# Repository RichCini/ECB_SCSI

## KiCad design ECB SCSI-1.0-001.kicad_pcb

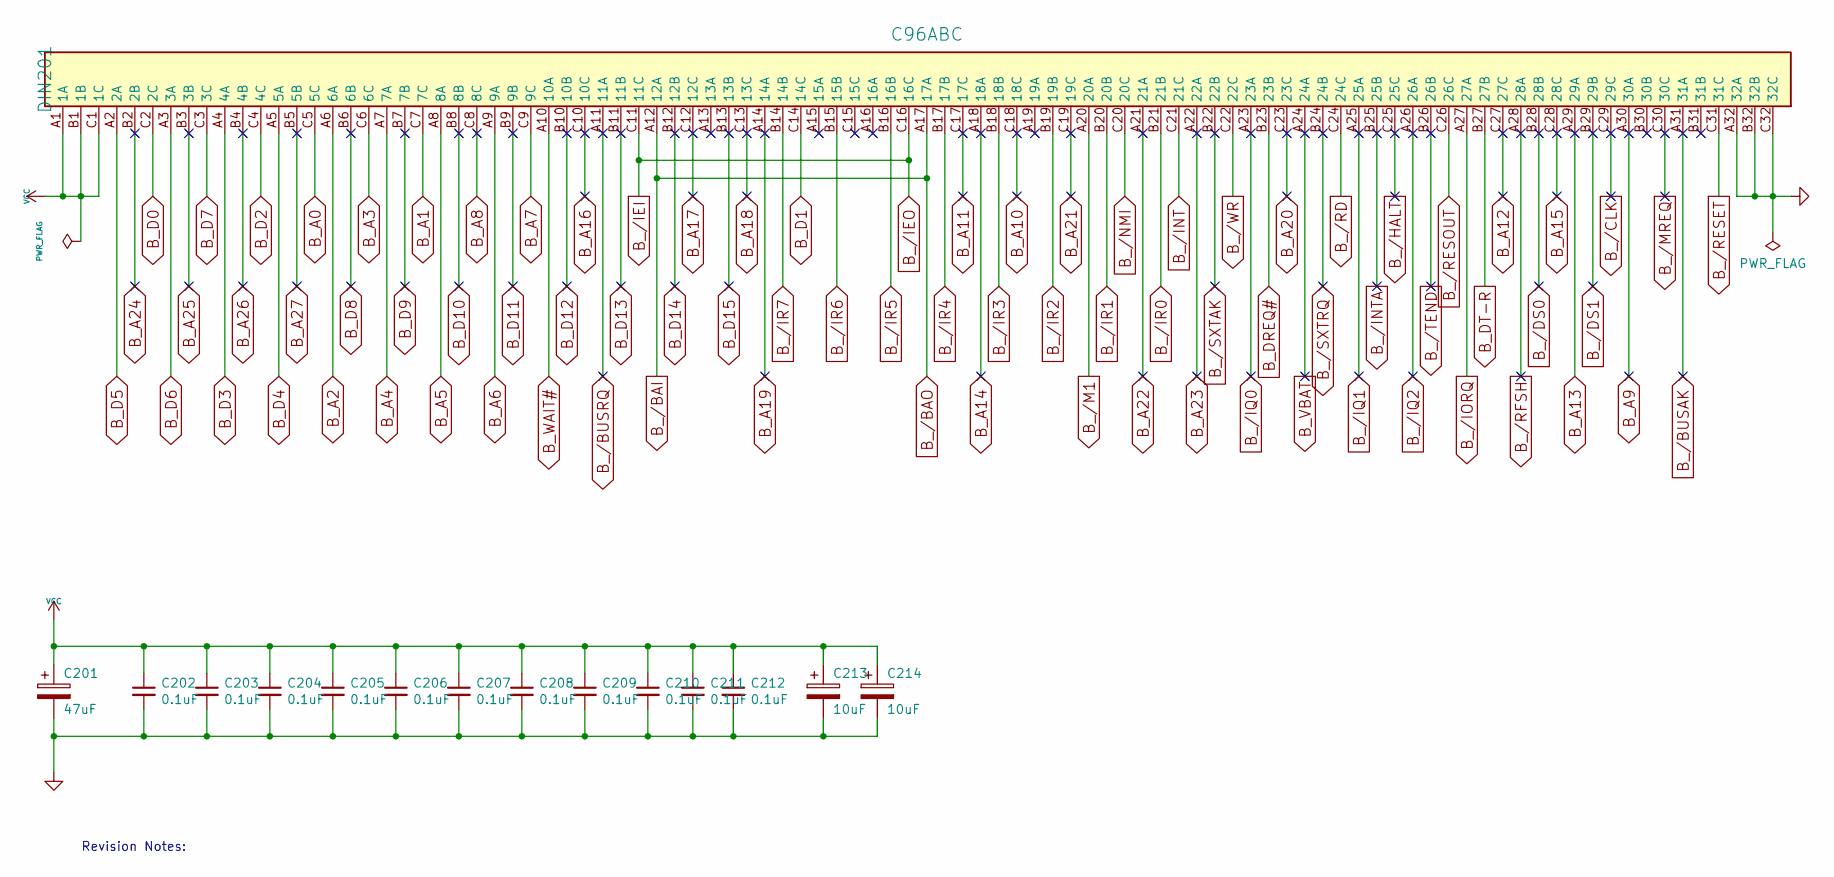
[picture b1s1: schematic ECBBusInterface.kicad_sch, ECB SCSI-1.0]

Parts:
C201: 47uF; CP_Radial_D7.5mm_P2.50mm
C202, C203, C204, C205, C206, C207, C208, C209, C210, C211, C212: 0.1uF; C_Disc_D4.3mm_W1.9mm_P5.00mm
C213, C214: 10uF; CP_Radial_D4.0mm_P1.50mm
DIN201: C96ABC; C96ABCM-RA

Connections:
B_/BAI: DIN201.A12 (12A), DIN201.A17 (17A)
B_/BUSAK: DIN201.A31 (31A)
B_/BUSRQ: DIN201.A11 (11A)
B_/CLK: DIN201.C29 (29C)
B_/DS0: DIN201.B28 (28B)
B_/DS1: DIN201.B29 (29B)
B_/HALT: DIN201.C25 (25C)
B_/IEI: DIN201.C11 (11C), DIN201.C16 (16C)
B_/INT: DIN201.C21 (21C); also elsewhere on the board
B_/INTA: DIN201.B25 (25B)
B_/IORQ: DIN201.A27 (27A); also elsewhere on the board
B_/IQ0: DIN201.A23 (23A)
B_/IQ1: DIN201.A25 (25A)
B_/IQ2: DIN201.A26 (26A)
B_/IR0: DIN201.B21 (21B); also elsewhere on the board
B_/IR1: DIN201.B20 (20B); also elsewhere on the board
B_/IR2: DIN201.B19 (19B); also elsewhere on the board
B_/IR3: DIN201.B18 (18B); also elsewhere on the board
B_/IR4: DIN201.B17 (17B); also elsewhere on the board
B_/IR5: DIN201.B16 (16B); also elsewhere on the board
B_/IR6: DIN201.B15 (15B); also elsewhere on the board
B_/IR7: DIN201.B14 (14B); also elsewhere on the board
B_/M1: DIN201.A20 (20A); also elsewhere on the board
B_/MREQ: DIN201.C30 (30C)
B_/NMI: DIN201.C20 (20C); also elsewhere on the board
B_/RD: DIN201.C24 (24C); also elsewhere on the board
B_/RESET: DIN201.C31 (31C); also elsewhere on the board
B_/RESOUT: DIN201.C26 (26C); also elsewhere on the board
B_/RFSH: DIN201.A28 (28A)
B_/SXTAK: DIN201.B22 (22B)
B_/SXTRQ: DIN201.B24 (24B)
B_/TEND: DIN201.B26 (26B)
B_/WR: DIN201.C22 (22C); also elsewhere on the board
B_A0: DIN201.C5 (5C); also elsewhere on the board
B_A1: DIN201.C7 (7C); also elsewhere on the board
B_A2: DIN201.A6 (6A); also elsewhere on the board
B_A3: DIN201.C6 (6C); also elsewhere on the board
B_A4: DIN201.A7 (7A); also elsewhere on the board
B_A5: DIN201.A8 (8A); also elsewhere on the board
B_A6: DIN201.A9 (9A); also elsewhere on the board
B_A7: DIN201.C9 (9C); also elsewhere on the board
B_A8: DIN201.C8 (8C)
B_A9: DIN201.A30 (30A)
B_A10: DIN201.C18 (18C)
B_A11: DIN201.C17 (17C)
B_A12: DIN201.C27 (27C)
B_A13: DIN201.A29 (29A)
B_A14: DIN201.A18 (18A)
B_A15: DIN201.C28 (28C)
B_A16: DIN201.C10 (10C)
B_A17: DIN201.C12 (12C)
B_A18: DIN201.C13 (13C)
B_A19: DIN201.A14 (14A)
B_A20: DIN201.C23 (23C)
B_A21: DIN201.C19 (19C)
B_A22: DIN201.A21 (21A)
B_A23: DIN201.A22 (22A)
B_A24: DIN201.B2 (2B)
B_A25: DIN201.B3 (3B)
B_A26: DIN201.B4 (4B)
B_A27: DIN201.B5 (5B)
B_D0: DIN201.C2 (2C); also elsewhere on the board
B_D1: DIN201.C14 (14C); also elsewhere on the board
B_D2: DIN201.C4 (4C); also elsewhere on the board
B_D3: DIN201.A4 (4A); also elsewhere on the board
B_D4: DIN201.A5 (5A); also elsewhere on the board
B_D5: DIN201.A2 (2A); also elsewhere on the board
B_D6: DIN201.A3 (3A); also elsewhere on the board
B_D7: DIN201.C3 (3C); also elsewhere on the board
B_D8: DIN201.B6 (6B)
B_D9: DIN201.B7 (7B)
B_D10: DIN201.B8 (8B)
B_D11: DIN201.B9 (9B)
B_D12: DIN201.B10 (10B)
B_D13: DIN201.B11 (11B)
B_D14: DIN201.B12 (12B)
B_D15: DIN201.B13 (13B)
B_DREQ#: DIN201.B23 (23B); also elsewhere on the board
B_DT-R: DIN201.B27 (27B); also elsewhere on the board
B_VBAT: DIN201.A24 (24A)
B_WAIT#: DIN201.A10 (10A); also elsewhere on the board
GND: C201.2, C202.2, C203.2, C204.2, C205.2, C206.2, C207.2, C208.2, C209.2, C210.2, C211.2, C212.2, C213.2, C214.2, DIN201.A32 (32A), DIN201.B32 (32B), DIN201.C32 (32C); also elsewhere on the board
VCC: C201.1, C202.1, C203.1, C204.1, C205.1, C206.1, C207.1, C208.1, C209.1, C210.1, C211.1, C212.1, C213.1, C214.1, DIN201.A1 (1A), DIN201.B1 (1B), DIN201.C1 (1C); also elsewhere on the board

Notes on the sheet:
Revision Notes:

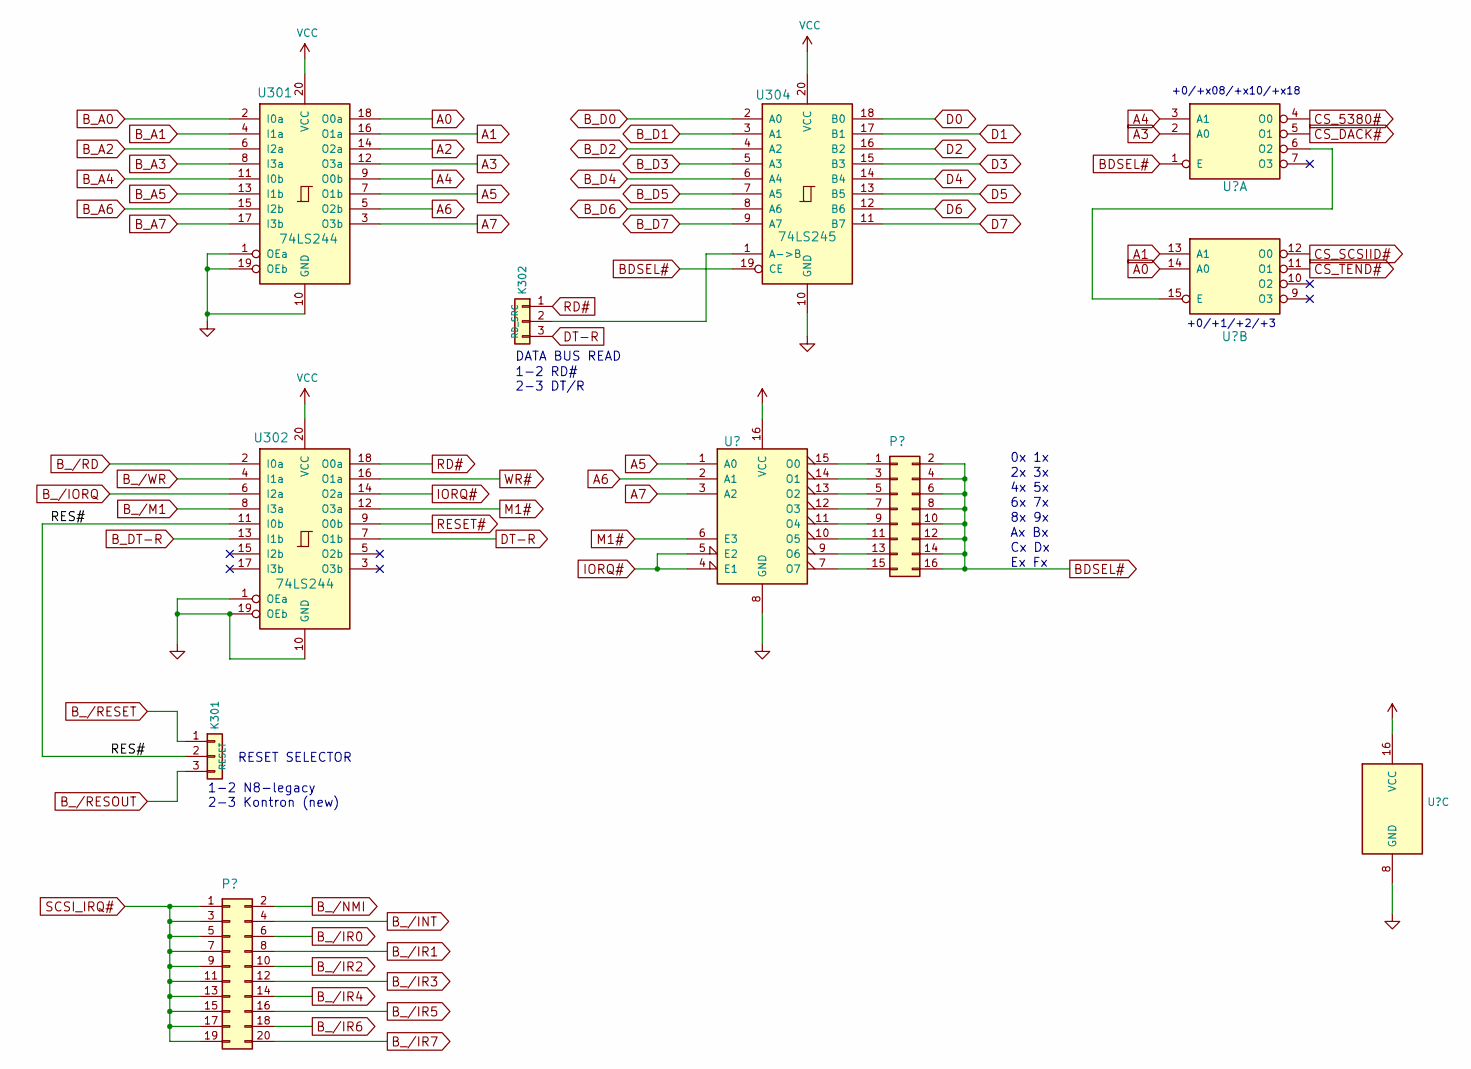
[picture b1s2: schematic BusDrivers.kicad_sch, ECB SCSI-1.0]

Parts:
K301: RESET; PinHeader_1x03_P2.54mm_Vertical
K302: RD_SRC; PinHeader_1x03_P2.54mm_Vertical
U301, U302: 74LS244; DIP-20_W7.62mm_Socket
U304: 74LS245; DIP-20_W7.62mm_Socket

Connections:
/Bus Drivers/RES#: K301.2, U302.11 (I0b)
A0: U301.18 (O0a); also elsewhere on the board
A1: U301.16 (O1a); also elsewhere on the board
A2: U301.14 (O2a); also elsewhere on the board
A3: U301.12 (O3a); also elsewhere on the board
A4: U301.9 (O0b); also elsewhere on the board
A5: U301.7 (O1b); also elsewhere on the board
A6: U301.5 (O2b); also elsewhere on the board
A7: U301.3 (O3b); also elsewhere on the board
BDSEL#: U304.19 (CE); also elsewhere on the board
B_/IORQ: U302.6 (I2a); also elsewhere on the board
B_/M1: U302.8 (I3a); also elsewhere on the board
B_/RD: U302.2 (I0a); also elsewhere on the board
B_/RESET: K301.1; also elsewhere on the board
B_/RESOUT: K301.3; also elsewhere on the board
B_/WR: U302.4 (I1a); also elsewhere on the board
B_A0: U301.2 (I0a); also elsewhere on the board
B_A1: U301.4 (I1a); also elsewhere on the board
B_A2: U301.6 (I2a); also elsewhere on the board
B_A3: U301.8 (I3a); also elsewhere on the board
B_A4: U301.11 (I0b); also elsewhere on the board
B_A5: U301.13 (I1b); also elsewhere on the board
B_A6: U301.15 (I2b); also elsewhere on the board
B_A7: U301.17 (I3b); also elsewhere on the board
B_D0: U304.2 (A0); also elsewhere on the board
B_D1: U304.3 (A1); also elsewhere on the board
B_D2: U304.4 (A2); also elsewhere on the board
B_D3: U304.5 (A3); also elsewhere on the board
B_D4: U304.6 (A4); also elsewhere on the board
B_D5: U304.7 (A5); also elsewhere on the board
B_D6: U304.8 (A6); also elsewhere on the board
B_D7: U304.9 (A7); also elsewhere on the board
B_DT-R: U302.13 (I1b); also elsewhere on the board
D0: U304.18 (B0); also elsewhere on the board
D1: U304.17 (B1); also elsewhere on the board
D2: U304.16 (B2); also elsewhere on the board
D3: U304.15 (B3); also elsewhere on the board
D4: U304.14 (B4); also elsewhere on the board
D5: U304.13 (B5); also elsewhere on the board
D6: U304.12 (B6); also elsewhere on the board
D7: U304.11 (B7); also elsewhere on the board
DT-R: K302.3, U302.7 (O1b)
GND: U301.1 (OEa), U301.10 (GND), U301.19 (OEb), U302.1 (OEa), U302.10 (GND), U302.19 (OEb), U304.10 (GND); also elsewhere on the board
IORQ#: U302.14 (O2a); also elsewhere on the board
M1#: U302.12 (O3a); also elsewhere on the board
unnamed: K302.2, U304.1 (A->B)
RD#: K302.1, U302.18 (O0a); also elsewhere on the board
RESET#: U302.9 (O0b); also elsewhere on the board
VCC: U301.20 (VCC), U302.20 (VCC), U304.20 (VCC); also elsewhere on the board
WR#: U302.16 (O1a); also elsewhere on the board

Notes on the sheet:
RESET SELECTOR
DATA BUS READ
1-2 N8-legacy 2-3 Kontron (new)
8x 9x
+0/+x08/+x10/+x18
0x 1x
6x 7x
2x 3x
Ax Bx
4x 5x
Cx Dx
1-2 RD# 2-3 DT/R
Ex Fx
+0/+1/+2/+3

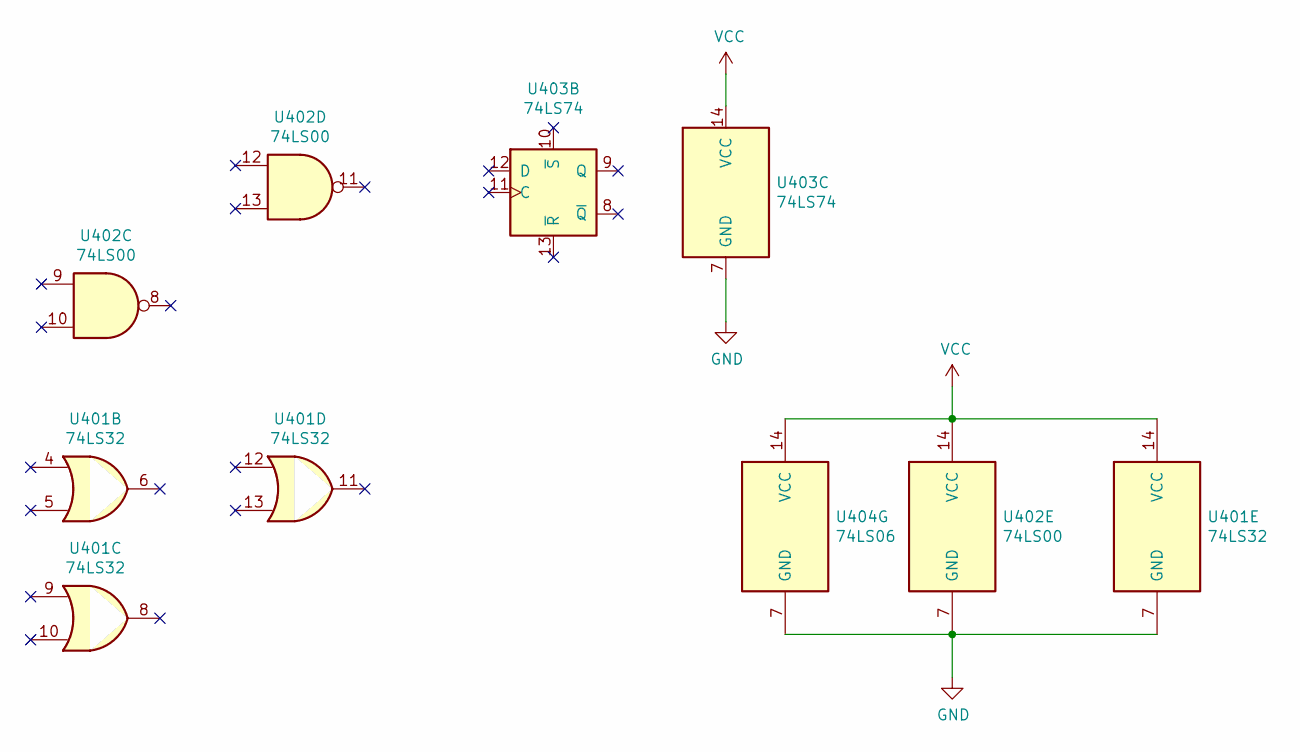
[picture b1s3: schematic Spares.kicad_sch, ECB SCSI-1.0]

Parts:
U401: 74LS32; DIP-14_W7.62mm_Socket
U402: 74LS00; DIP-14_W7.62mm_Socket
U403: 74LS74
U404: 74LS06; DIP-14_W7.62mm_Socket

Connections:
GND: U401.7 (GND), U402.7 (GND), U403.7 (GND), U404.7 (GND); also elsewhere on the board
unnamed 177: U402.4, U402.5; also elsewhere on the board
unnamed 178: U402.6; also elsewhere on the board
VCC: U401.14 (VCC), U402.14 (VCC), U403.14 (VCC), U404.14 (VCC); also elsewhere on the board

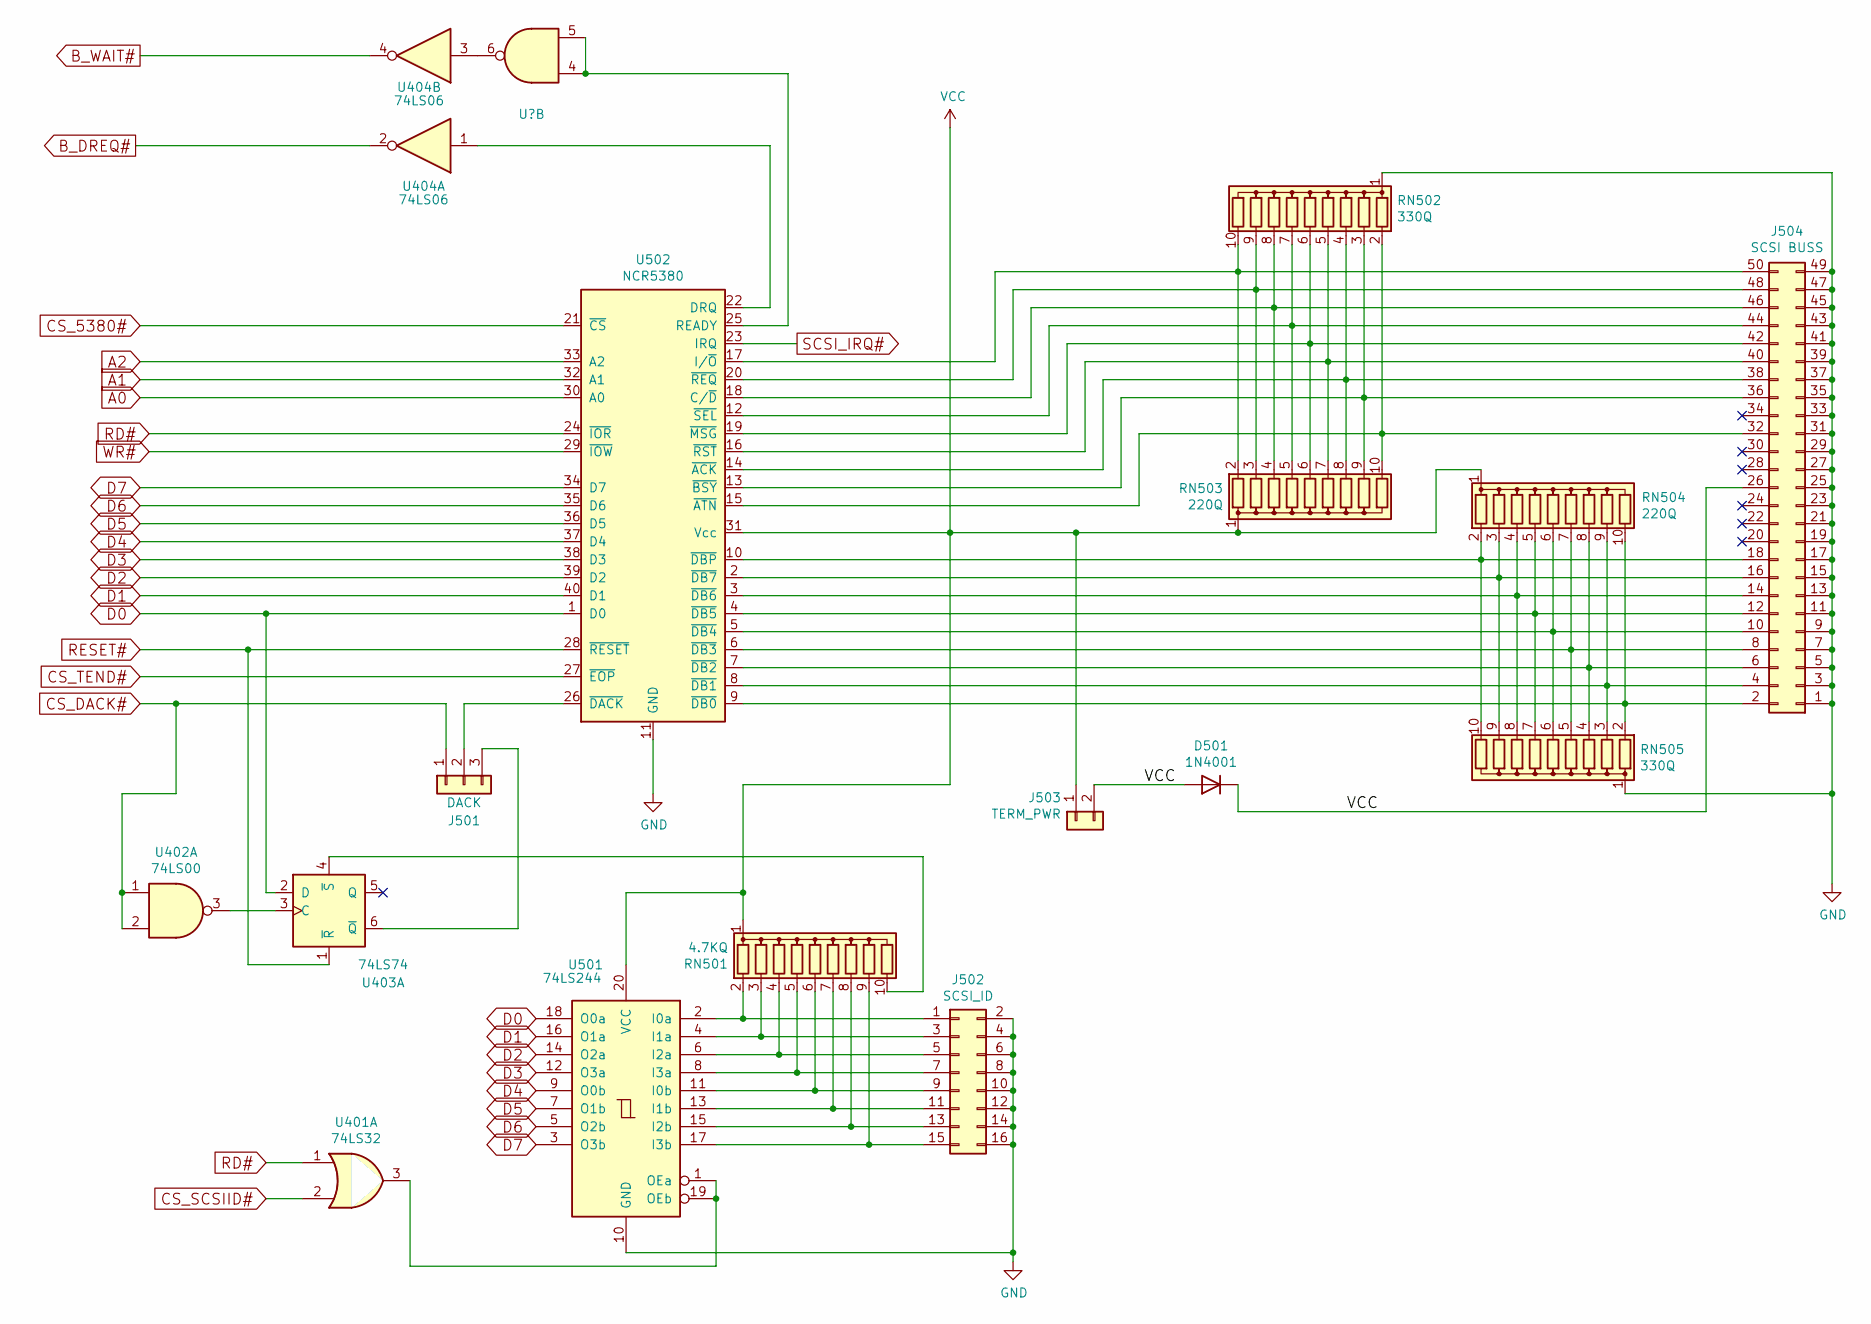
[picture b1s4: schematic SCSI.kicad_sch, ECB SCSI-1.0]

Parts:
D501: 1N4001; D_DO-41_SOD81_P10.16mm_Horizontal
J501: DACK; PinHeader_1x03_P2.54mm_Vertical
J502: SCSI_ID; PinHeader_2x08_P2.54mm_Vertical
J503: TERM_PWR; PinHeader_1x02_P2.54mm_Vertical
J504: SCSI BUSS; PinHeader_2x25_P2.54mm_Horizontal
RN501: 4.7KQ; R_Array_SIP10
RN502, RN505: 330Q; R_Array_SIP10
RN503, RN504: 220Q; R_Array_SIP10
U401: 74LS32
U402: 74LS00
U403: 74LS74; DIP-14_W7.62mm_Socket
U404: 74LS06
U501: 74LS244; DIP-20_W7.62mm_Socket
U502: NCR5380; DIP-40_W15.24mm

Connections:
A0: U502.30 (A0); also elsewhere on the board
A1: U502.32 (A1); also elsewhere on the board
A2: U502.33 (A2); also elsewhere on the board
B_DREQ#: U404.2; also elsewhere on the board
B_WAIT#: U404.4; also elsewhere on the board
CS_5380#: U502.21 (~CS); also elsewhere on the board
CS_DACK#: J501.1, U402.1, U402.2; also elsewhere on the board
CS_SCSIID#: U401.2; also elsewhere on the board
CS_TEND#: U502.27 (~EOP); also elsewhere on the board
D0: U403.2 (D), U501.18 (O0a), U502.1 (D0); also elsewhere on the board
D1: U501.16 (O1a), U502.40 (D1); also elsewhere on the board
D2: U501.14 (O2a), U502.39 (D2); also elsewhere on the board
D3: U501.12 (O3a), U502.38 (D3); also elsewhere on the board
D4: U501.9 (O0b), U502.37 (D4); also elsewhere on the board
D5: U501.7 (O1b), U502.36 (D5); also elsewhere on the board
D6: U501.5 (O2b), U502.35 (D6); also elsewhere on the board
D7: U501.3 (O3b), U502.34 (D7); also elsewhere on the board
GND: J502.2, J502.4, J502.6, J502.8, J502.10, J502.12, J502.14, J502.16, J504.1, J504.3, J504.5, J504.7, J504.9, J504.11, J504.13, J504.15, J504.17, J504.19, J504.21, J504.23, J504.25, J504.27, J504.29, J504.31, J504.33, J504.35, J504.37, J504.39, J504.41, J504.43, J504.45, J504.47, J504.49, RN502.1 (common), RN505.1 (common), U501.10 (GND), U502.11 (GND); also elsewhere on the board
unnamed: J501.2, U502.26 (~DACK)
unnamed: J501.3, U403.6 (~Q)
unnamed: J502.1, RN501.2 (R1), U501.2 (I0a)
unnamed: J502.3, RN501.3 (R2), U501.4 (I1a)
unnamed: J502.5, RN501.4 (R3), U501.6 (I2a)
unnamed: J502.7, RN501.5 (R4), U501.8 (I3a)
unnamed: J502.9, RN501.6 (R5), U501.11 (I0b)
unnamed: J502.11, RN501.7 (R6), U501.13 (I1b)
unnamed: J502.13, RN501.8 (R7), U501.15 (I2b)
unnamed: J502.15, RN501.9 (R8), U501.17 (I3b)
unnamed: J504.2, RN504.10 (R9), RN505.2 (R1), U502.9 (~DB0)
unnamed: J504.4, RN504.9 (R8), RN505.3 (R2), U502.8 (~DB1)
unnamed: J504.6, RN504.8 (R7), RN505.4 (R3), U502.7 (~DB2)
unnamed: J504.8, RN504.7 (R6), RN505.5 (R4), U502.6 (~DB3)
unnamed: J504.10, RN504.6 (R5), RN505.6 (R5), U502.5 (~DB4)
unnamed: J504.12, RN504.5 (R4), RN505.7 (R6), U502.4 (~DB5)
unnamed: J504.14, RN504.4 (R3), RN505.8 (R7), U502.3 (~DB6)
unnamed: J504.16, RN504.3 (R2), RN505.9 (R8), U502.2 (~DB7)
unnamed: J504.18, RN504.2 (R1), RN505.10 (R9), U502.10 (~DBP)
unnamed: J504.32, RN502.2 (R1), RN503.10 (R9), U502.15 (~ATN)
unnamed: J504.36, RN502.3 (R2), RN503.9 (R8), U502.13 (~BSY)
unnamed: J504.38, RN502.4 (R3), RN503.8 (R7), U502.14 (~ACK)
unnamed: J504.40, RN502.5 (R4), RN503.7 (R6), U502.16 (~RST)
unnamed: J504.42, RN502.6 (R5), RN503.6 (R5), U502.19 (~MSG)
unnamed: J504.44, RN502.7 (R6), RN503.5 (R4), U502.12 (~SEL)
unnamed: J504.46, RN502.8 (R7), RN503.4 (R3), U502.18 (C/~D)
unnamed: J504.48, RN502.9 (R8), RN503.3 (R2), U502.20 (~REQ)
unnamed: J504.50, RN502.10 (R9), RN503.2 (R1), U502.17 (I/~O)
unnamed: RN501.10 (R9), U403.4 (~S)
unnamed: U401.3, U501.1 (OEa), U501.19 (OEb)
unnamed: U402.3, U403.3 (C)
unnamed: U402.4, U402.5, U502.25 (READY)
unnamed: U402.6, U404.3
unnamed: U404.1, U502.22 (DRQ)
RD#: U401.1, U502.24 (~IOR); also elsewhere on the board
RESET#: U403.1 (~R), U502.28 (~RESET); also elsewhere on the board
SCSI_IRQ#: U502.23 (IRQ); also elsewhere on the board
VCC: J503.1, RN501.1 (common), RN503.1 (common), RN504.1 (common), U501.20 (VCC), U502.31 (Vcc); also elsewhere on the board
WR#: U502.29 (~IOW); also elsewhere on the board

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
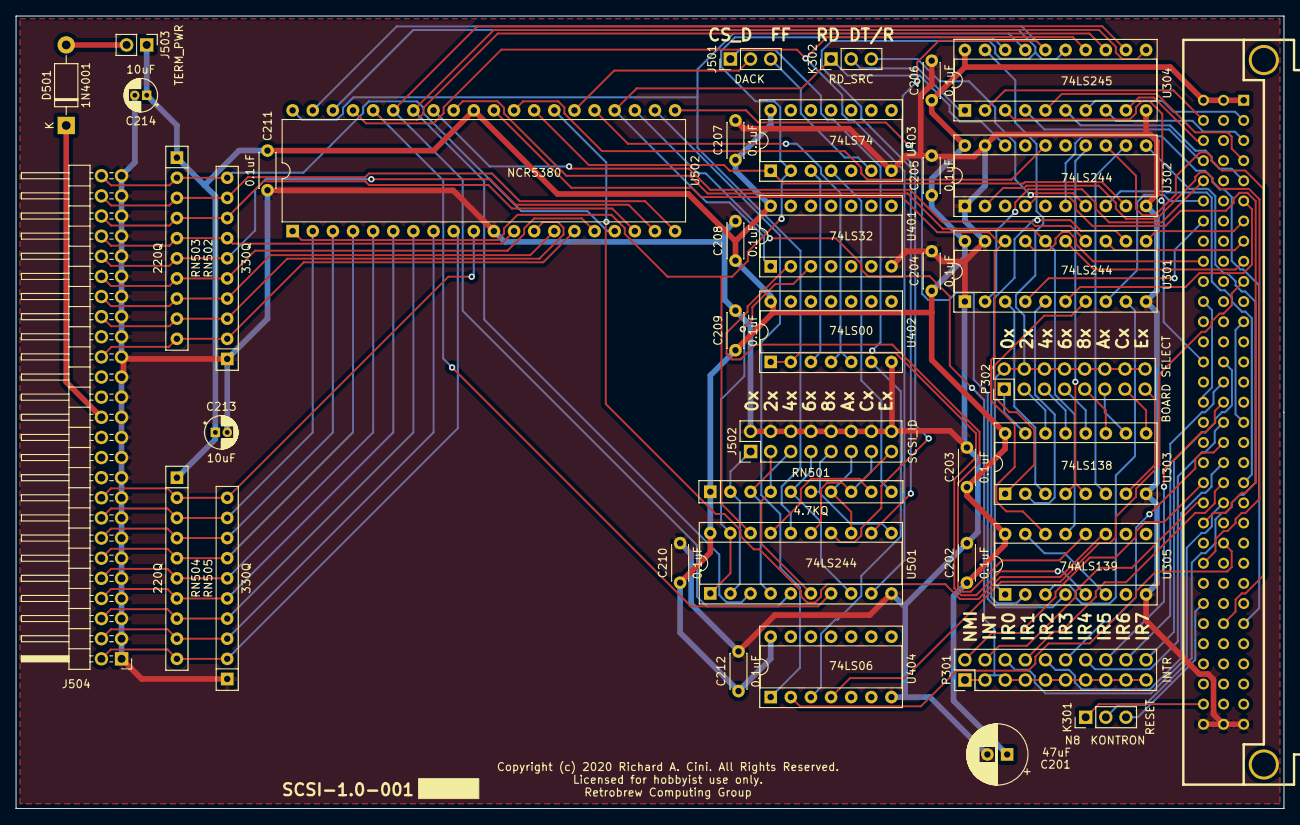
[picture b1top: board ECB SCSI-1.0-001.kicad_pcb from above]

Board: 2 copper layers, 160.0 x 100.0 mm, 40 parts (0 on the bottom side), 114 nets.

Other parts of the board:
P301: INTR; PinHeader_2x10_P2.54mm_Vertical
P302: BOARD SELECT; PinHeader_2x08_P2.54mm_Vertical
U303: 74LS138; DIP-16_W7.62mm_Socket
U305: 74ALS139; DIP-16_W7.62mm_Socket

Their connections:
A0: U305.14; also elsewhere on the board
A1: U305.13; also elsewhere on the board
A3: U305.2; also elsewhere on the board
A4: U305.3; also elsewhere on the board
A5: U303.1; also elsewhere on the board
A6: U303.2; also elsewhere on the board
A7: U303.3; also elsewhere on the board
BDSEL#: P302.2, P302.4, P302.6, P302.8, P302.10, P302.12, P302.14, P302.16, U305.1; also elsewhere on the board
B_/INT: P301.4; also elsewhere on the board
B_/IR0: P301.6; also elsewhere on the board
B_/IR1: P301.8; also elsewhere on the board
B_/IR2: P301.10; also elsewhere on the board
B_/IR3: P301.12; also elsewhere on the board
B_/IR4: P301.14; also elsewhere on the board
B_/IR5: P301.16; also elsewhere on the board
B_/IR6: P301.18; also elsewhere on the board
B_/IR7: P301.20; also elsewhere on the board
B_/NMI: P301.2; also elsewhere on the board
CS_5380#: U305.4; also elsewhere on the board
CS_DACK#: U305.5; also elsewhere on the board
CS_SCSIID#: U305.12; also elsewhere on the board
CS_TEND#: U305.11; also elsewhere on the board
GND: U303.8, U305.8; also elsewhere on the board
IORQ#: U303.4, U303.5; also elsewhere on the board
M1#: U303.6; also elsewhere on the board
unnamed: P302.1, U303.15
unnamed: P302.3, U303.14
unnamed: P302.5, U303.13
unnamed: P302.7, U303.12
unnamed: P302.9, U303.11
unnamed: P302.11, U303.10
unnamed: P302.13, U303.9
unnamed: P302.15, U303.7
unnamed: U305.6, U305.15
SCSI_IRQ#: P301.1, P301.3, P301.5, P301.7, P301.9, P301.11, P301.13, P301.15, P301.17, P301.19; also elsewhere on the board
VCC: U303.16, U305.16; also elsewhere on the board

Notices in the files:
BusDrivers.kicad_sch:
Copyright (c) 2020 Richard Cini. All Rights Reserved.
ECB SCSI-1.0-001.kicad_pcb:
Copyright (c) 2020 Richard A. Cini. All Rights Reserved.
